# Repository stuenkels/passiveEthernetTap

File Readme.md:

# 10/100 Passive Ethernet Tap with support for POE
Passive LAN tap for monitoring 10/100 networks \
Uses SS-90000-011 Ethernet port, https://www.mouser.com/ProductDetail/530-SS-90000-011

## 3d View

## PCB image

## Finished board
TODO: Add images of finished board

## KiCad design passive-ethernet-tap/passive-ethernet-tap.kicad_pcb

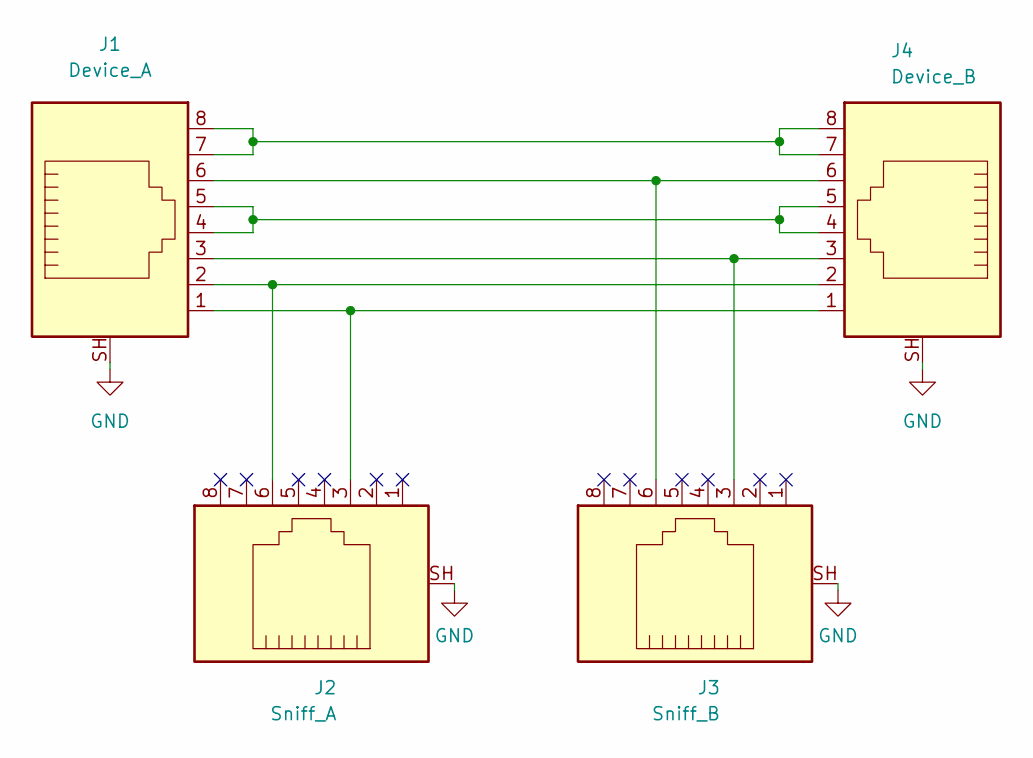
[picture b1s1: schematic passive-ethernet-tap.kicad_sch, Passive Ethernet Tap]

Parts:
J1: Device_A; Bel Fuse SS-90000-011
J2: Sniff_A; Bel Fuse SS-90000-011
J3: Sniff_B; Bel Fuse SS-90000-011
J4: Device_B; Bel Fuse SS-90000-011

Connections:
GND: J1.SH, J2.SH, J3.SH, J4.SH
unnamed: J1.1, J2.3, J4.1
unnamed: J1.2, J2.6, J4.2
unnamed: J1.3, J3.3, J4.3
unnamed: J1.4, J1.5, J4.4, J4.5
unnamed: J1.6, J3.6, J4.6
unnamed: J1.7, J1.8, J4.7, J4.8

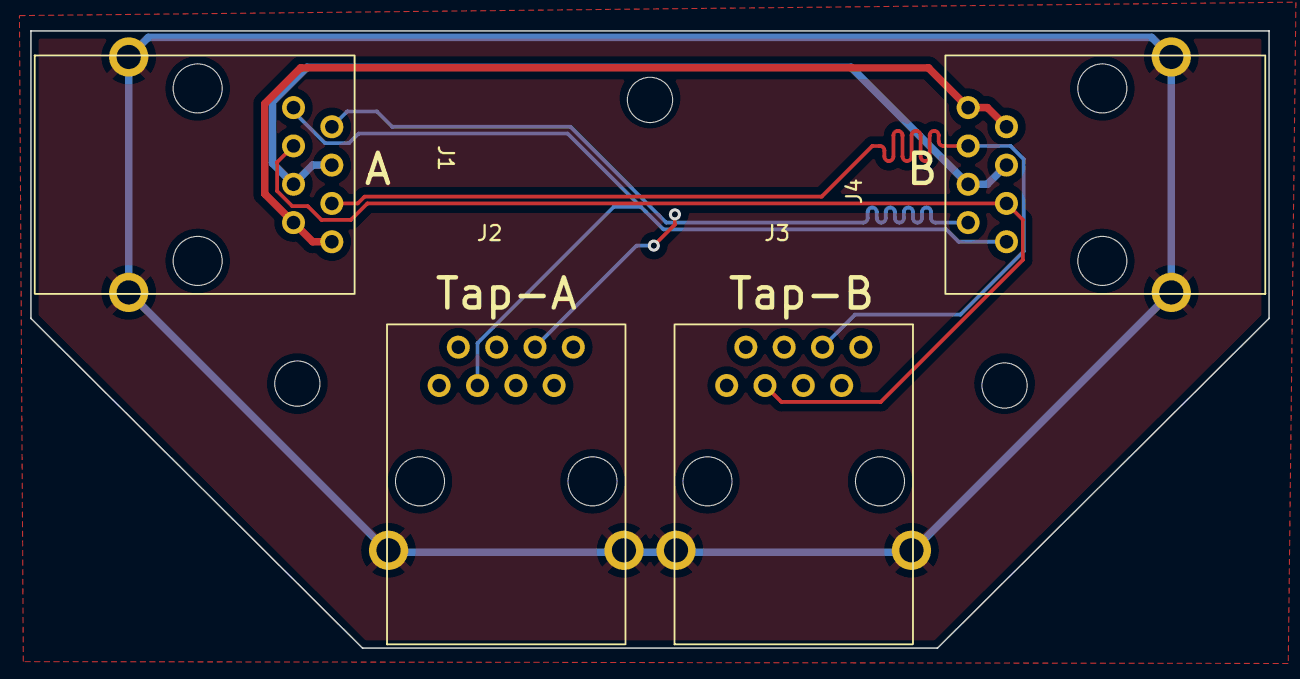
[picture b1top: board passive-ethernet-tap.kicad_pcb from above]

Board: 2 copper layers, 82.0 x 40.9 mm, 4 parts (0 on the bottom side), 7 nets.

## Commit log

2024-11-30 init
2024-11-30 minor typo fix
2024-11-30 added new pretty pictures
2024-11-30 typo fix
2024-11-30 Apparently mounting holes dissapeared
